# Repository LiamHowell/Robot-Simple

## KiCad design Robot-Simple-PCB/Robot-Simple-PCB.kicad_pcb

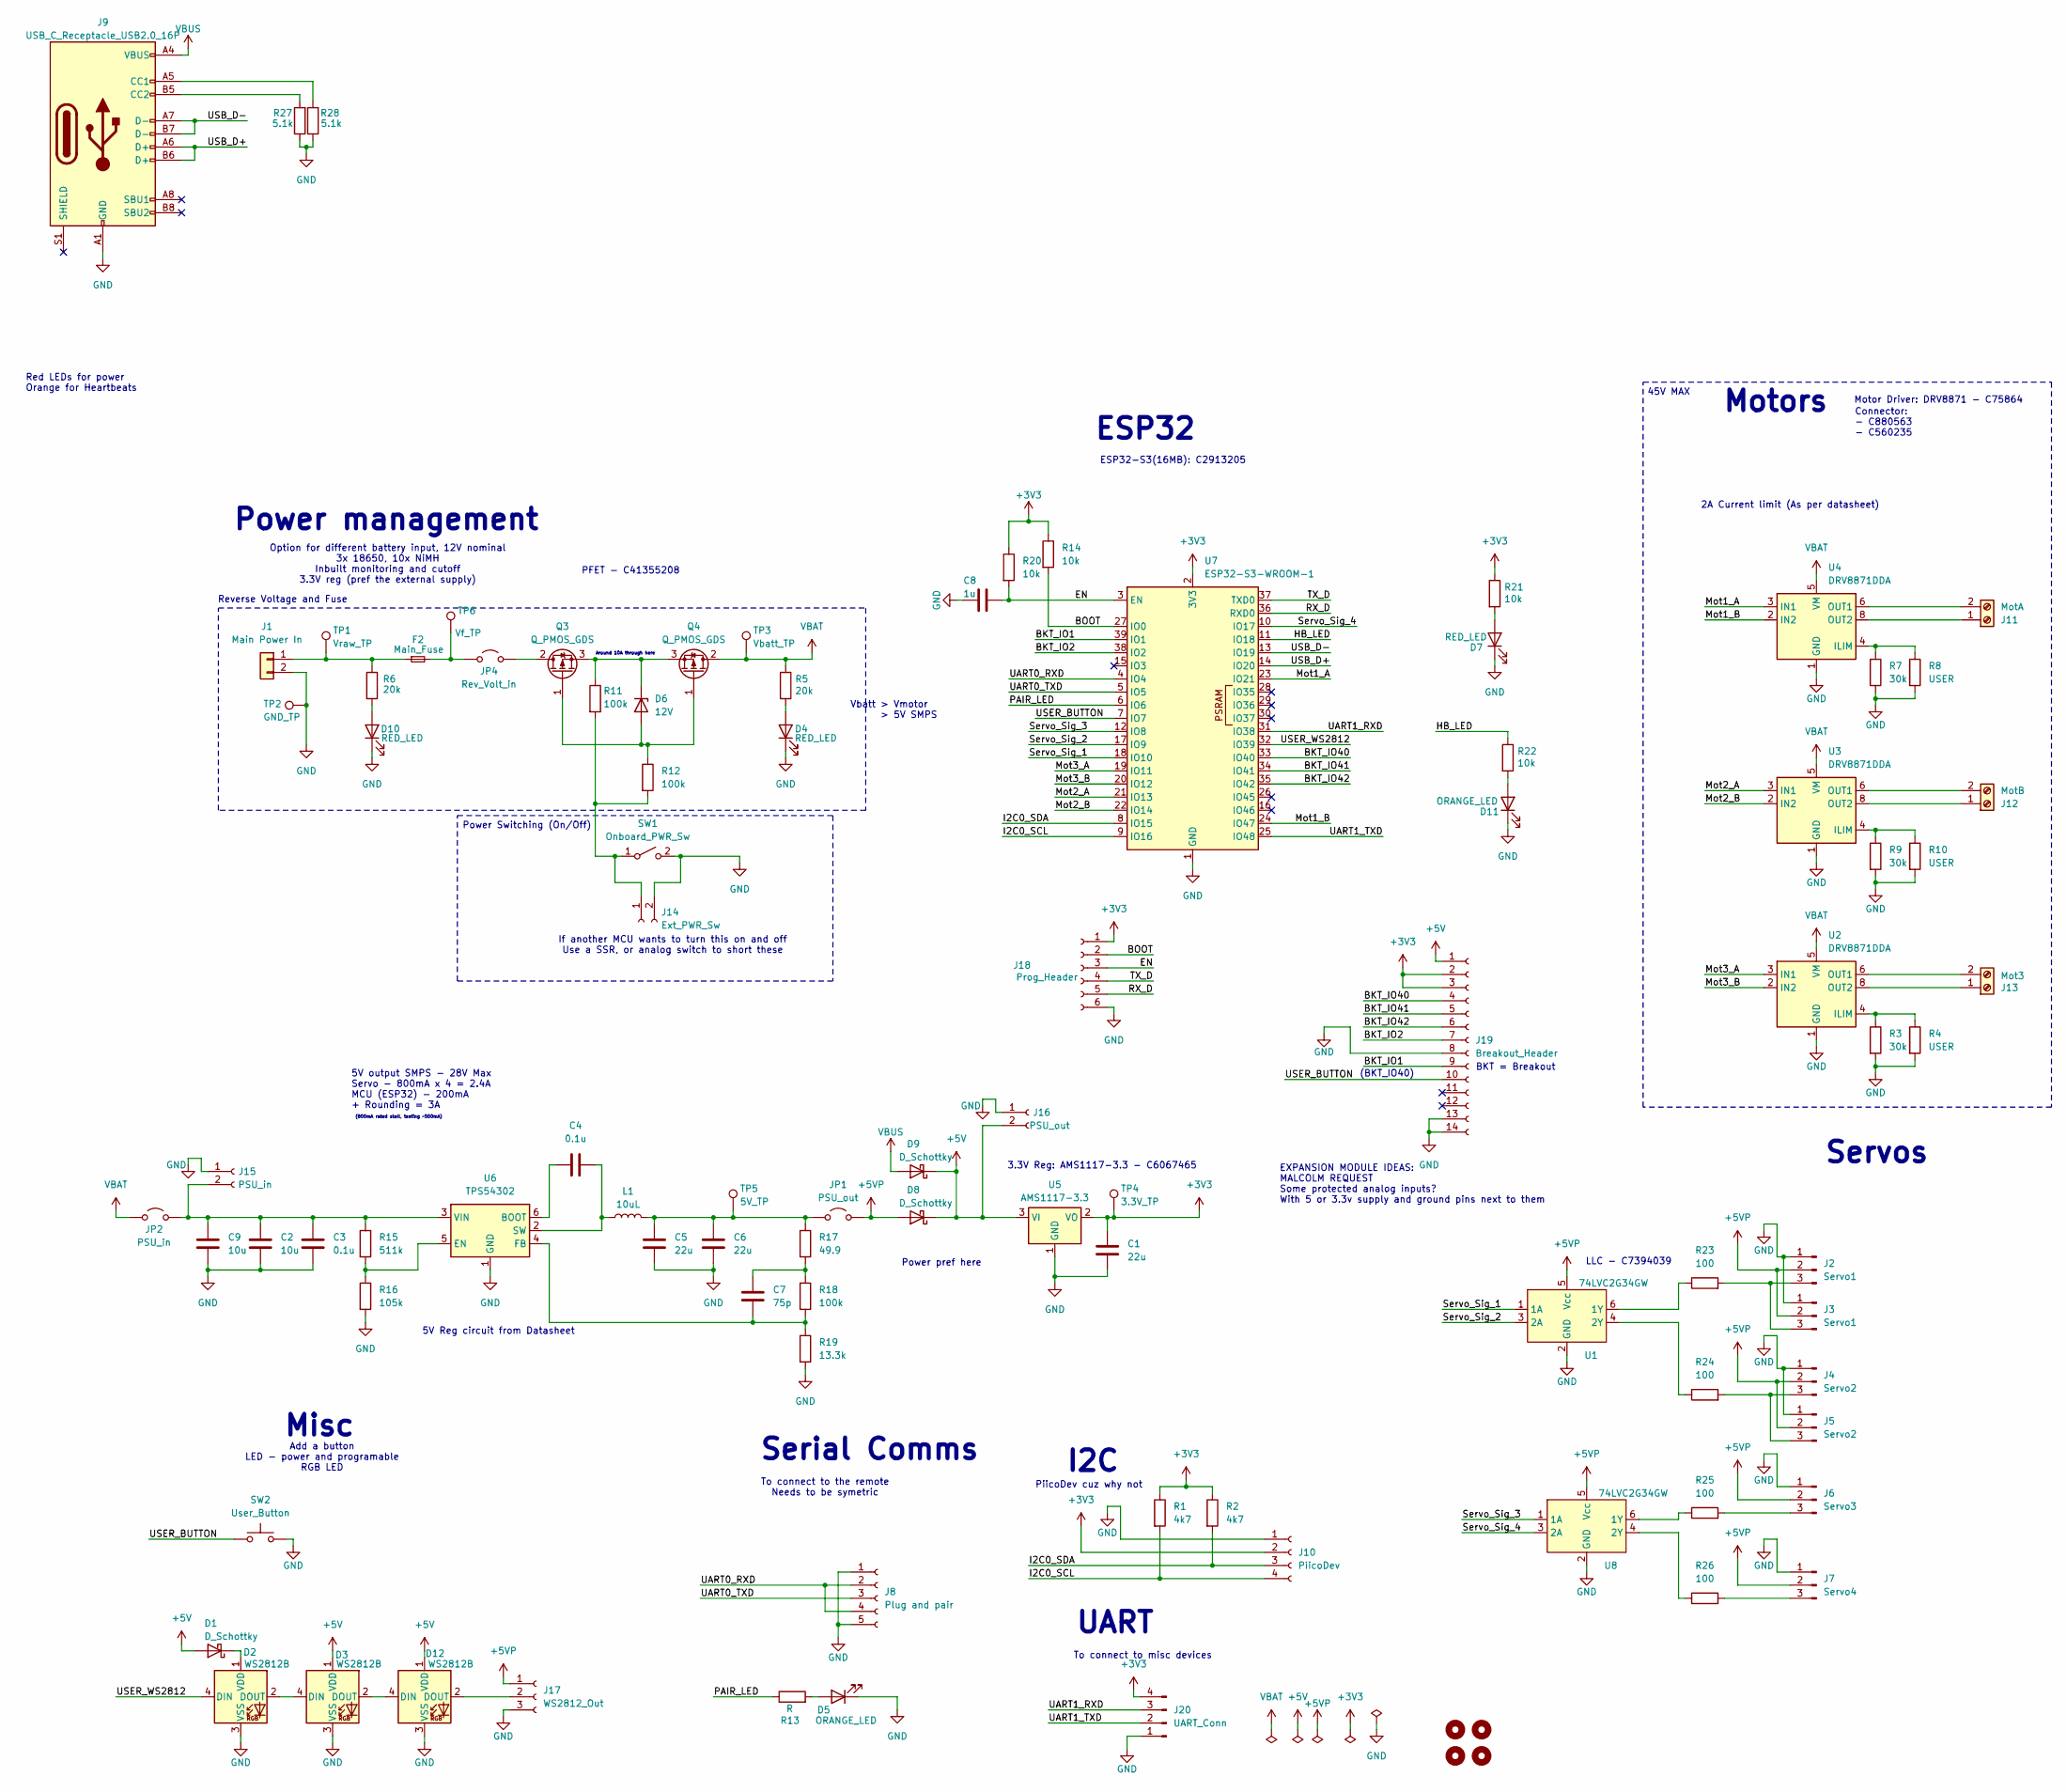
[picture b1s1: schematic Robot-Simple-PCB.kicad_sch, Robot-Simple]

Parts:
C1, C5, C6: 22u; C_1206_3216Metric; MPN C1523
C2, C9: 10u; C_1206_3216Metric; MPN C13585
C3, C4: 0.1u; C_0603_1608Metric; MPN C14663
C7: 75p; C_0402_1005Metric; MPN C1546
C8: 1u; C_0402_1005Metric; MPN C52923
D1, D8, D9: D_Schottky; D_SOD-123; MPN C8598
D2, D3, D12: WS2812B; LED_WS2812B_PLCC4_5.0x5.0mm_P3.2mm; MPN C5349953
D4, D7, D10: RED_LED; LED_0603_1608Metric
D5, D11: ORANGE_LED; LED_0603_1608Metric
D6: 12V; LED_0603_1608Metric
F2: Main_Fuse; Fuseholder_Littelfuse_Nano2_154x
H1, H2, H3, H4: MountingHole; MountingHole_4.3mm_M4
J1: Main Power In; PhoenixContact_MCV_1,5_2-G-3.5_1x02_P3.50mm_Vertical
J2, J3: Servo1; PinHeader_1x03_P2.54mm_Vertical
J4, J5: Servo2; PinHeader_1x03_P2.54mm_Vertical
J6: Servo3; PinHeader_1x03_P2.54mm_Vertical
J7: Servo4; PinHeader_1x03_P2.54mm_Vertical
J8: Plug and pair; PinSocket_1x05_P2.54mm_Vertical
J9: USB_C_Receptacle_USB2.0_16P; USB_C_Receptacle_HCTL_HC-TYPE-C-16P-01A; MPN C2894897
J10: PiicoDev; JST_SH_SM04B-SRSS-TB_1x04-1MP_P1.00mm_Horizontal
J11: MotA; PhoenixContact_MCV_1,5_2-G-3.5_1x02_P3.50mm_Vertical
J12: MotB; PhoenixContact_MCV_1,5_2-G-3.5_1x02_P3.50mm_Vertical
J13: Mot3; PhoenixContact_MCV_1,5_2-G-3.5_1x02_P3.50mm_Vertical
J14: Ext_PWR_Sw; PinHeader_1x02_P2.54mm_Vertical
J15: PSU_in; PinHeader_1x02_P2.54mm_Vertical
J16: PSU_out; PinHeader_1x02_P2.54mm_Vertical
J17: WS2812_Out; PinHeader_1x03_P2.54mm_Vertical
J18: Prog_Header; PinHeader_1x06_P2.54mm_Vertical
J19: Breakout_Header; PinHeader_1x14_P2.54mm_Vertical
J20: UART_Conn; PinHeader_1x04_P2.54mm_Vertical
JP1: PSU_out; SolderJumper-2_P1.3mm_Open_RoundedPad1.0x1.5mm
JP2: PSU_in; SolderJumper-2_P1.3mm_Open_RoundedPad1.0x1.5mm
JP4: Rev_Volt_in; SolderJumper-2_P1.3mm_Open_RoundedPad1.0x1.5mm
L1: 10uL; L_Chilisin_BMRB00060612; MPN C128692
Q3, Q4: Q_PMOS_GDS; TO-252-2; MPN C41355208
R1, R2: 4k7; R_0402_1005Metric_Pad0.72x0.64mm_HandSolder
R3, R7, R9: 30k; R_0402_1005Metric_Pad0.72x0.64mm_HandSolder
R4, R8, R10: USER; R_Axial_DIN0207_L6.3mm_D2.5mm_P10.16mm_Horizontal
R5, R6: 20k; R_0402_1005Metric_Pad0.72x0.64mm_HandSolder
R11, R12, R18: 100k; R_0402_1005Metric_Pad0.72x0.64mm_HandSolder
R13: R; R_0402_1005Metric_Pad0.72x0.64mm_HandSolder
R14, R20, R21, R22: 10k; R_0402_1005Metric_Pad0.72x0.64mm_HandSolder
R15: 511k; R_0402_1005Metric_Pad0.72x0.64mm_HandSolder
R16: 105k; R_0402_1005Metric_Pad0.72x0.64mm_HandSolder
R17: 49.9; R_0402_1005Metric_Pad0.72x0.64mm_HandSolder
R19: 13.3k; R_0402_1005Metric_Pad0.72x0.64mm_HandSolder
R23, R24, R25, R26: 100; R_0402_1005Metric_Pad0.72x0.64mm_HandSolder
R27, R28: 5.1k; R_0402_1005Metric_Pad0.72x0.64mm_HandSolder
SW1: Onboard_PWR_Sw; SW_SPDT_PCM12; MPN C431541
SW2: User_Button; SW_Push_1P1T_NO_6x6mm_H9.5mm; MPN C7470157
TP1: Vraw_TP; TestPoint_THTPad_D1.0mm_Drill0.5mm
TP2: GND_TP; TestPoint_THTPad_D1.0mm_Drill0.5mm
TP3: Vbatt_TP; TestPoint_THTPad_D1.0mm_Drill0.5mm
TP4: 3.3V_TP; TestPoint_THTPad_D1.0mm_Drill0.5mm
TP5: 5V_TP; TestPoint_THTPad_D1.0mm_Drill0.5mm
TP6: Vf_TP; TestPoint_THTPad_D1.0mm_Drill0.5mm
U1, U8: 74LVC2G34GW; SOT-23-6
U2, U3: DRV8871DDA; Texas_HTSOP-8-1EP_3.9x4.9mm_P1.27mm_EP2.95x4.9mm_Mask2.4x3.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
U4: DRV8871DDA; Texas_HTSOP-8-1EP_3.9x4.9mm_P1.27mm_EP2.95x4.9mm_Mask2.4x3.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; MPN C75864
U5: AMS1117-3.3; SOT-223-3_TabPin2; MPN C6067465
U6: TPS54302; SOT-23-6
U7: ESP32-S3-WROOM-1

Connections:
+3V3: C1.1, J10.2, J18.1, J19.2, J19.3, J20.4, R1.1, R2.1, R14.1, R20.1, R21.1, TP4.1, U5.2 (VO), U7.2 (3V3)
+5V: D1.2 (A), D3.1 (VDD), D8.1 (K), D9.1 (K), D12.1 (VDD), J16.2, J19.1, U5.3 (VI)
+5VP: D8.2 (A), J2.2, J3.2, J4.2, J5.2, J6.2, J7.2, J17.1, JP1.2 (B), U1.5 (Vcc), U8.5 (Vcc)
/BKT_IO1: J19.9, U7.39 (IO1)
/BKT_IO2: J19.7, U7.38 (IO2)
/BKT_IO40: J19.4, U7.33 (IO40)
/BKT_IO41: J19.5, U7.34 (IO41)
/BKT_IO42: J19.6, U7.35 (IO42)
/BOOT: J18.2, R14.2, U7.27 (IO0)
/EN: C8.1, J18.3, R20.2, U7.3 (EN)
/HB_LED: R22.1, U7.11 (IO18)
/I2C0_SCL: J10.4, R1.2, U7.9 (IO16)
/I2C0_SDA: J10.3, R2.2, U7.8 (IO15)
/Mot1_A: U4.3 (IN1), U7.23 (IO21)
/Mot1_B: U4.2 (IN2), U7.24 (IO47)
/Mot2_A: U3.3 (IN1), U7.21 (IO13)
/Mot2_B: U3.2 (IN2), U7.22 (IO14)
/Mot3_A: U2.3 (IN1), U7.19 (IO11)
/Mot3_B: U2.2 (IN2), U7.20 (IO12)
/PAIR_LED: R13.1, U7.6 (IO6)
/RX_D: J18.5, U7.36 (RXD0)
/Servo_Sig_1: U1.1 (1A), U7.18 (IO10)
/Servo_Sig_2: U1.3 (2A), U7.17 (IO9)
/Servo_Sig_3: U7.12 (IO8), U8.1 (1A)
/Servo_Sig_4: U7.10 (IO17), U8.3 (2A)
/TX_D: J18.4, U7.37 (TXD0)
/UART0_RXD: J8.2, J8.4, U7.4 (IO4)
/UART0_TXD: J8.3, U7.5 (IO5)
/UART1_RXD: J20.3, U7.31 (IO38)
/UART1_TXD: J20.2, U7.25 (IO48)
/USB_D+: J9.A6 (D+), J9.B6 (D+), U7.14 (IO20)
/USB_D-: J9.A7 (D-), J9.B7 (D-), U7.13 (IO19)
/USER_BUTTON: J19.10, SW2.1, U7.7 (IO7)
/USER_WS2812: D2.4 (DIN), U7.32 (IO39)
GND: C1.2, C2.2, C3.2, C5.2, C6.2, C8.2, C9.2, D2.3 (VSS), D3.3 (VSS), D4.1 (K), D5.1 (K), D7.1 (K), D10.1 (K), D11.1 (K), D12.3 (VSS), J1.2, J2.1, J3.1, J4.1, J5.1, J6.1, J7.1, J8.1, J8.5, J9.A1 (GND), J9.A12 (GND), J9.B1 (GND), J9.B12 (GND), J10.1, J14.2, J15.1, J16.1, J17.3, J18.6, J19.8, J19.13, J19.14, J20.1, R3.2, R4.2, R7.2, R8.2, R9.2, R10.2, R16.2, R19.2, R27.1, R28.1, SW1.2 (B), SW2.2, TP2.1, U1.2 (GND), U2.1 (GND), U2.7 (GND), U2.9 (GND), U3.1 (GND), U3.7 (GND), U3.9 (GND), U4.1 (GND), U4.7 (GND), U4.9 (GND), U5.1 (GND), U6.1 (GND), U7.1 (GND), U7.40 (GND), U7.41 (GND), U8.2 (GND)
unnamed: C7.1, R17.2, R18.1
unnamed: D1.1 (K), D2.1 (VDD)
unnamed: D2.2 (DOUT), D3.4 (DIN)
unnamed: D4.2 (A), R5.2
unnamed: D5.2 (A), R13.2
unnamed: D6.2 (A), Q3.1 (G), Q4.1 (G), R12.1
unnamed: D6.1 (K), Q3.3 (S), Q4.3 (S), R11.1
unnamed: D7.2 (A), R21.2
unnamed: D10.2 (A), R6.2
unnamed: D11.2 (A), R22.2
unnamed: D3.2 (DOUT), D12.4 (DIN)
unnamed: D12.2 (DOUT), J17.2
unnamed: F2.1, J1.1, R6.1, TP1.1
unnamed: J2.3, J3.3, R23.2
unnamed: J4.3, J5.3, R24.2
unnamed: J6.3, R25.2
unnamed: J7.3, R26.2
unnamed: J9.A5 (CC1), R28.2
unnamed: J9.B5 (CC2), R27.2
unnamed: J11.1, U4.8 (OUT2)
unnamed: J11.2, U4.6 (OUT1)
unnamed: J12.1, U3.8 (OUT2)
unnamed: J12.2, U3.6 (OUT1)
unnamed: J13.1, U2.8 (OUT2)
unnamed: J13.2, U2.6 (OUT1)
unnamed: J14.1, R11.2, R12.2, SW1.1 (A)
unnamed: C2.1, C3.1, C9.1, J15.2, JP2.2 (B), R15.1, U6.3 (VIN)
unnamed: C5.1, C6.1, JP1.1 (A), L1.2, R17.1, TP5.1
unnamed: F2.2, JP4.1 (A), TP6.1
unnamed: JP4.2 (B), Q3.2 (D)
unnamed: R23.1, U1.6 (1Y)
unnamed: R24.1, U1.4 (2Y)
unnamed: R3.1, R4.1, U2.4 (ILIM)
unnamed: R9.1, R10.1, U3.4 (ILIM)
unnamed: R7.1, R8.1, U4.4 (ILIM)
unnamed: C4.1, U6.6 (BOOT)
unnamed: R15.2, R16.1, U6.5 (EN)
unnamed: C7.2, R18.2, R19.1, U6.4 (FB)
unnamed: C4.2, L1.1, U6.2 (SW)
unnamed: R25.1, U8.6 (1Y)
unnamed: R26.1, U8.4 (2Y)
VBAT: JP2.1 (A), Q4.2 (D), R5.1, TP3.1, U2.5 (VM), U3.5 (VM), U4.5 (VM)
VBUS: D9.2 (A), J9.A4 (VBUS), J9.A9 (VBUS), J9.B4 (VBUS), J9.B9 (VBUS)

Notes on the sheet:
(800mA rated stall, testing ~500mA)
ESP32
ESP32-S3(16MB): C2913205
PiicoDev cuz why not
(BKT_IO40)
Power management
Servos
Serial Comms
EXPANSION MODULE IDEAS: MALCOLM REQUEST Some protected analog inputs? With 5 or 3.3v supply and ground pins next to them
I2C
Red LEDs for power Orange for Heartbeats
Connector: - C880563 - C560235
Add a button LED - power and programable RGB LED
Power pref here
If another MCU wants to turn this on and off Use a SSR, or analog switch to short these
Motors
PFET - C41355208
To connect to misc devices
To connect to the remote Needs to be symetric
Power Switching (On/Off)
45V MAX
3.3V Reg: AMS1117-3.3 - C6067465
Motor Driver: DRV8871 - C75864
LLC - C7394039
UART
Reverse Voltage and Fuse
Around 10A through here
2A Current limit (As per datasheet)
BKT = Breakout
Misc
Option for different battery input, 12V nominal 3x 18650, 10x NiMH Inbuilt monitoring and cutoff 3.3V reg (pref the external supply)
5V output SMPS - 28V Max Servo - 800mA x 4 = 2.4A MCU (ESP32) - 200mA + Rounding = 3A
5V Reg circuit from Datasheet
Vbatt > Vmotor > 5V SMPS

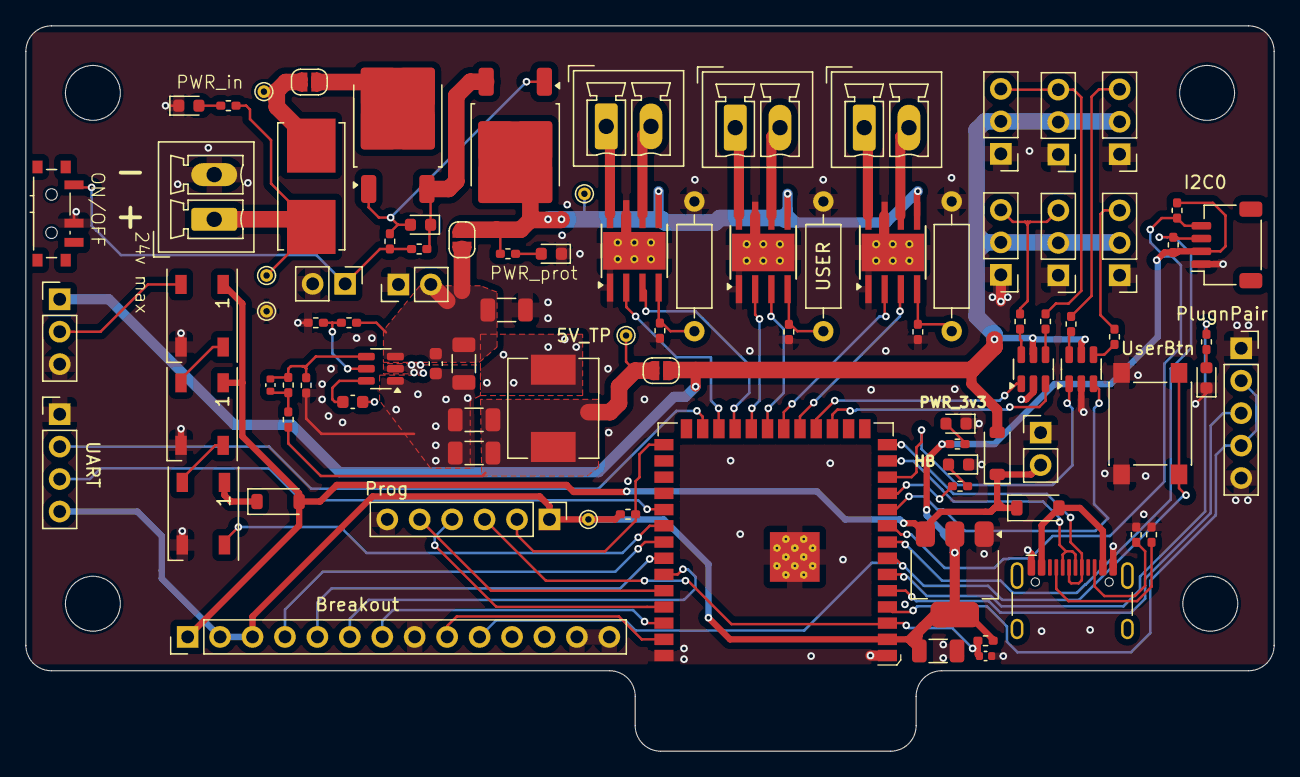
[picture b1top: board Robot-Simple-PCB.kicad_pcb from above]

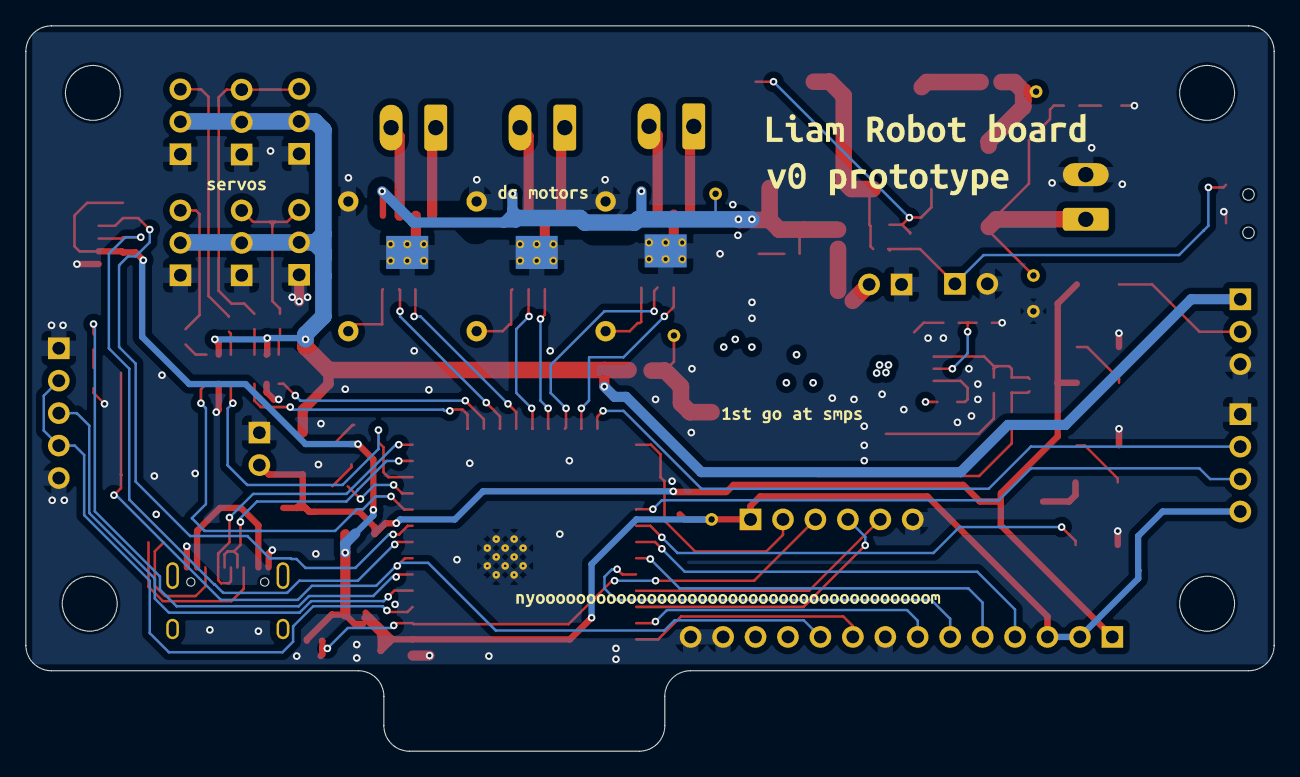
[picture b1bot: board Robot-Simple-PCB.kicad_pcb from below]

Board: 4 copper layers, 97.7 x 56.8 mm, 102 parts (6 on the bottom side), 78 nets.

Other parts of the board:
kibuzzard-67CD1FB0: G***; kibuzzard-67CD1FB0
kibuzzard-67CD1FBD: G***; kibuzzard-67CD1FBD
kibuzzard-67CD201A: G***; kibuzzard-67CD201A
kibuzzard-67CD2000: G***; kibuzzard-67CD2000
kibuzzard-67CD2025: G***; kibuzzard-67CD2025
kibuzzard-67CD2035: G***; kibuzzard-67CD2035

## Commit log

2025-02-19 Some schema stuff
2025-03-06 More workin
2025-03-08 Schematic complete, started routing
2025-03-08 Yuuuuh
2025-03-09 Done?
2025-05-05 Some changes!
